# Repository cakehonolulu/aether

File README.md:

# aether

## Current prototype, excuse my poor soldering...

## Breadboard running with an Arduino GIGA as a bus arbitrer

## Board schematic

## 3D model of the PCB (Missing some models)

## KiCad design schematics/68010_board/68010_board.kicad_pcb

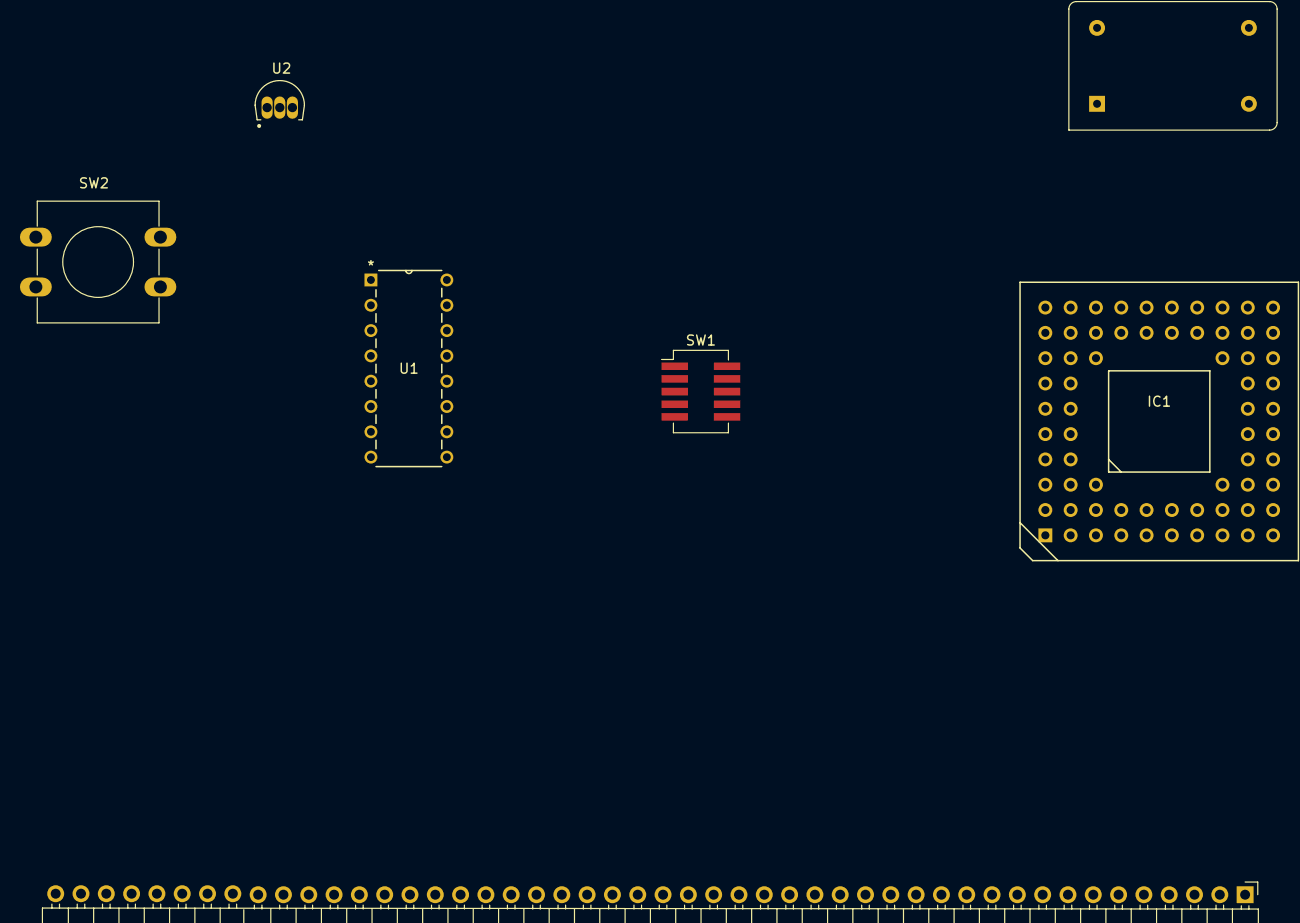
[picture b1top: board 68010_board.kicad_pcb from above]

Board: 2 copper layers, 7 parts (0 on the bottom side), 53 nets, no tracks yet.

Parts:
IC1: MC68010R; PGA64
J1: 48-bit bus; PinHeader_1x48_P2.54mm_Horizontal
SW1: CLK DIP Switch; SW_DIP_SPSTx05_Slide_KingTek_DSHP05TJ_W5.25mm_P1.27mm_JPin
SW2: Reset; SW_PUSH-12mm
U1: SN74HC4040N
U2: DS1813-5; TO92127P495H695-3
X1: Crystal Oscillator; Oscillator_DIP-14

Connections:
+5V: IC1.C01 (BGACK), IC1.D01 (BR), IC1.D02 (Vcc), IC1.E09 (Vcc), IC1.G02 (VPA), IC1.H02 (IPL2), IC1.H03 (IPL1), IC1.J01 (BERR), IC1.J02 (IPL0), J1.48, U1.16 (VCC), U2.2 (VCC), X1.14 (Vcc)
/A1: IC1.K04 (A1), J1.23
/AS: IC1.A02 (AS), J1.40
/CLK: IC1.E01 (CLK), J1.46, SW1.6, SW1.7, SW1.8, SW1.9, SW1.10
/D0: IC1.B04 (D0), J1.39
/D15: IC1.B10 (D15), J1.24
/HALT: IC1.F01 (HALT), IC1.F02 (RESET), J1.44, J1.45, SW2.2, U2.1 (~RST)
/LDS: IC1.B02 (LDS), J1.42
/R/W: IC1.C03 (R/W), J1.43
/UDS: IC1.B03 (UDS), J1.41
GND: IC1.B01 (DTACK), IC1.D09 (GND), IC1.E02 (GND), J1.47, SW2.1, U1.8 (GND), U2.3 (GND), X1.7 (GND)
unnamed: IC1.J05 (A2), J1.22
unnamed: IC1.K05 (A3), J1.21
unnamed: IC1.K06 (A4), J1.20
unnamed: IC1.J06 (A5), J1.19
unnamed: IC1.K07 (A6), J1.18
unnamed: IC1.K08 (A7), J1.17
unnamed: IC1.J07 (A8), J1.16
unnamed: IC1.K09 (A9), J1.15
unnamed: IC1.J08 (A10), J1.14
unnamed: IC1.J09 (A11), J1.13
unnamed: IC1.H09 (A12), J1.12
unnamed: IC1.H08 (A13), J1.11
unnamed: IC1.J10 (A14), J1.10
unnamed: IC1.G09 (A15), J1.9
unnamed: IC1.H10 (A16), J1.8
unnamed: IC1.G10 (A17), J1.7
unnamed: IC1.F09 (A18), J1.6
unnamed: IC1.F10 (A19), J1.5
unnamed: IC1.E10 (A20), J1.4
unnamed: IC1.D10 (A21), J1.3
unnamed: IC1.C10 (A22), J1.2
unnamed: IC1.C09 (A23), J1.1
unnamed: IC1.A03 (D1), J1.38
unnamed: IC1.A04 (D2), J1.37
unnamed: IC1.B05 (D3), J1.36
unnamed: IC1.A05 (D4), J1.35
unnamed: IC1.A06 (D5), J1.34
unnamed: IC1.B06 (D6), J1.33
unnamed: IC1.A07 (D7), J1.32
unnamed: IC1.A08 (D8), J1.31
unnamed: IC1.B07 (D9), J1.30
unnamed: IC1.A09 (D10), J1.29
unnamed: IC1.B08 (D11), J1.28
unnamed: IC1.A10 (D12), J1.27
unnamed: IC1.C08 (D13), J1.26
unnamed: IC1.B09 (D14), J1.25
unnamed: U1.10 (CLK), X1.8 (OUT)
unnamed: SW1.1, U1.9 (QA)
unnamed: SW1.2, U1.7 (QB)
unnamed: SW1.3, U1.6 (QC)
unnamed: SW1.4, U1.5 (QD)
unnamed: SW1.5, U1.3 (QE)

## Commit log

2024-10-17 schematic: Add basic 68010 attachable board
2024-10-20 aether: Upload base 68010 board KiCad schematic
2024-11-06 aether: Add updated schematics (64->80 pin header, future-proofing)
2024-11-06 README.md: Show images
